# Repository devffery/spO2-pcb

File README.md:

# spO2-pcb

# SpO2 Measurement PCB

## Overview
This project is a custom PCB designed in KiCad for an SpO2 (blood oxygen saturation) monitoring circuit.

## Features
- Photodiode sensing circuit
- LED driver for IR and red LEDs
- Signal conditioning stage
- Microcontroller interface

## Tools Used
- KiCad 9
- GitHub for version control

## Files Included
- Schematic
- PCB layout
- Gerber files
- Custom footprint libraries

## PCB Preview

## Future Improvements
- Improve analog filtering
- Add better power regulation

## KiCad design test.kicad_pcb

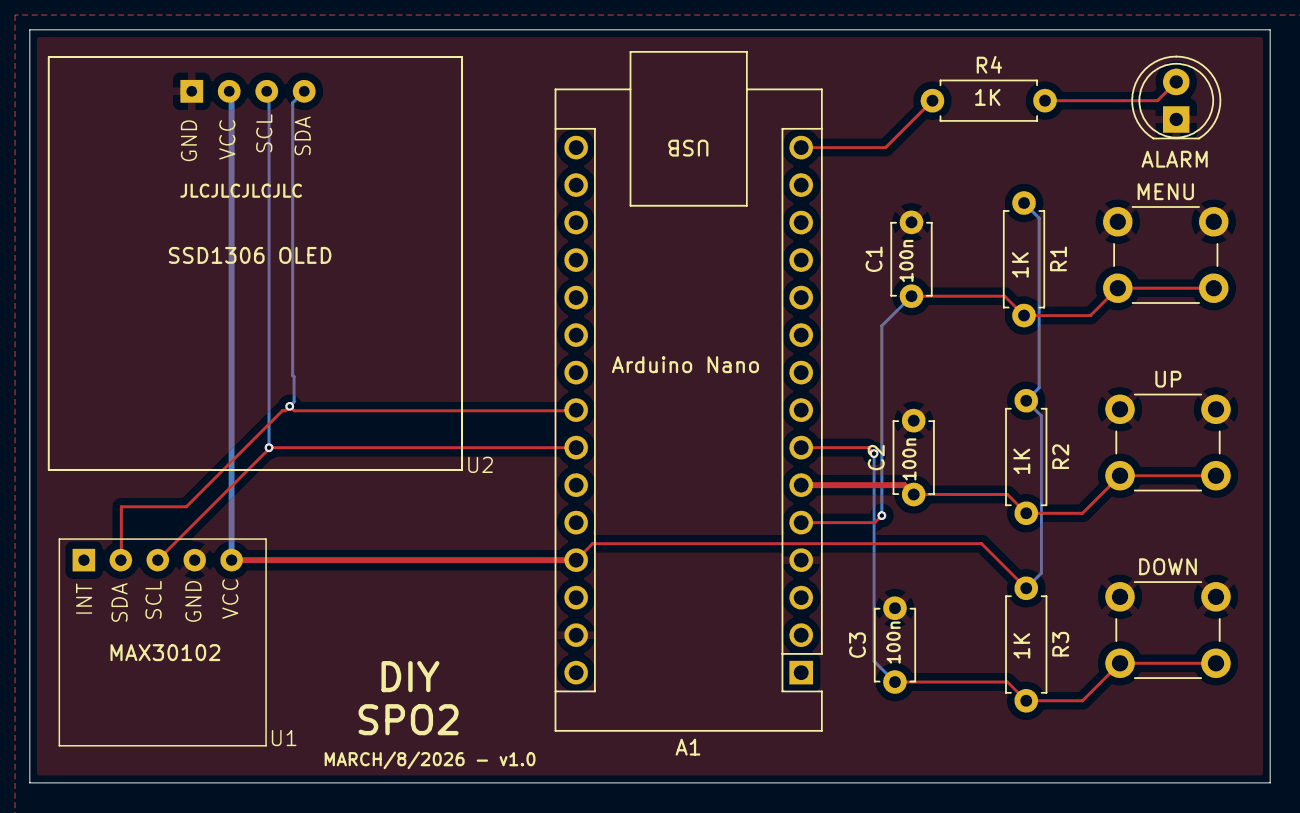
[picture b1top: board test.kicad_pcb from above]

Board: 4 copper layers, 84.0 x 51.0 mm, 14 parts (0 on the bottom side), 9 nets.

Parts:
A1: Arduino_Nano_v3.x; Arduino_Nano
ALARM: LED; LED_D5.0mm
C1, C2, C3: 100n; C_Disc_D4.7mm_W2.5mm_P5.00mm
DOWN: SW_Push; SW_PUSH_6mm
MENU: SW_Push; SW_PUSH_6mm
R1, R2, R3, R4: 1K; R_Axial_DIN0207_L6.3mm_D2.5mm_P7.62mm_Horizontal
U1: MAX30102
U2: SSD1306
UP: SW_Push; SW_PUSH_6mm

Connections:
+5V: A1.27 (+5V), R1.1, R2.1, R3.1, U1.5 (VCC), U2.2 (VCC)
GND: A1.4 (GND), A1.29 (GND), ALARM.1 (K), C1.2, C2.2, C3.2, DOWN.1, MENU.1, U1.4 (GND), U2.1 (GND), UP.1
unnamed: A1.23 (A4), U1.2 (SDA), U2.4 (SDA)
unnamed: A1.24 (A5), U1.3 (SCL), U2.3 (SCL)
unnamed: A1.5 (D2), C1.1, MENU.2, R1.2
unnamed: A1.6 (D3), C2.1, R2.2, UP.2
unnamed: A1.7 (D4), C3.1, DOWN.2, R3.2
unnamed: A1.15 (D12), R4.1
unnamed: ALARM.2 (A), R4.2

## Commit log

2026-03-09 Expand README with project details and features
    Added project overview, features, tools used, included files, PCB preview, and future improvements sections.
2026-03-09 Add PCB preview image to README
    Added PCB preview image to README.
2026-03-09 Update README with new images and future improvements
    Added additional PCB preview images and outlined future improvements.
2026-03-09 SpO2 PCB design
